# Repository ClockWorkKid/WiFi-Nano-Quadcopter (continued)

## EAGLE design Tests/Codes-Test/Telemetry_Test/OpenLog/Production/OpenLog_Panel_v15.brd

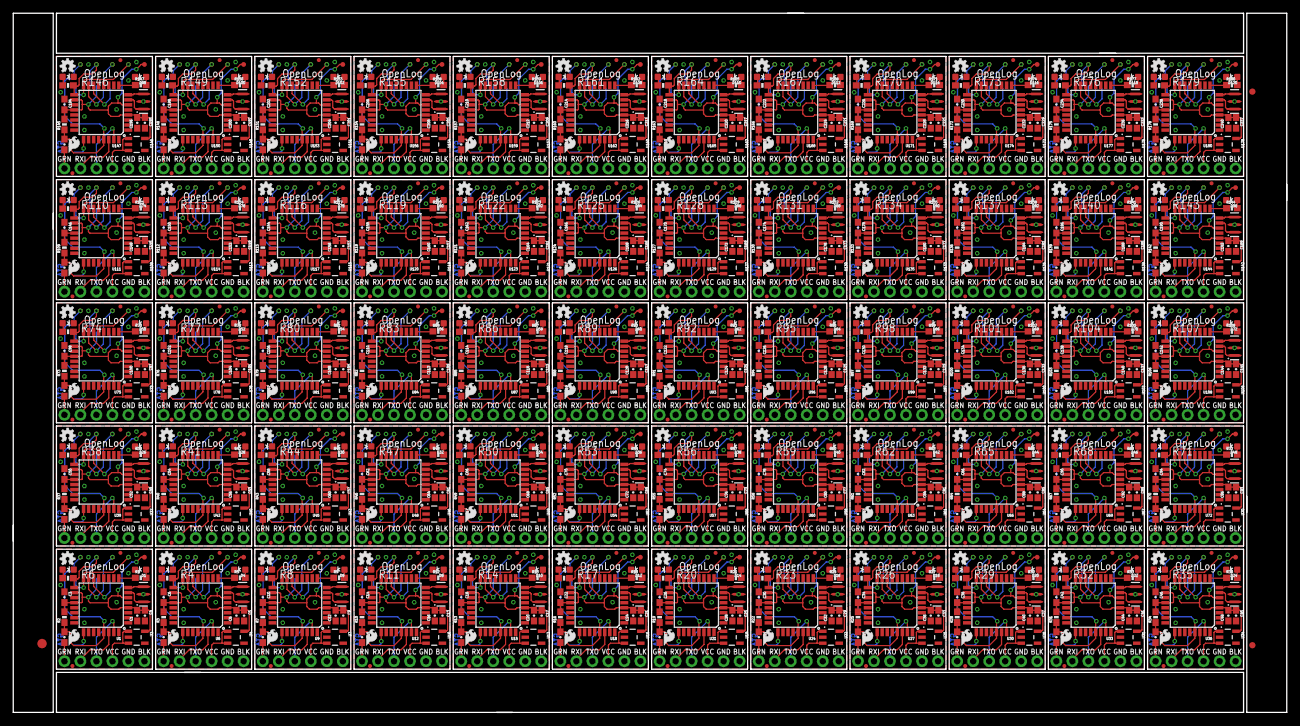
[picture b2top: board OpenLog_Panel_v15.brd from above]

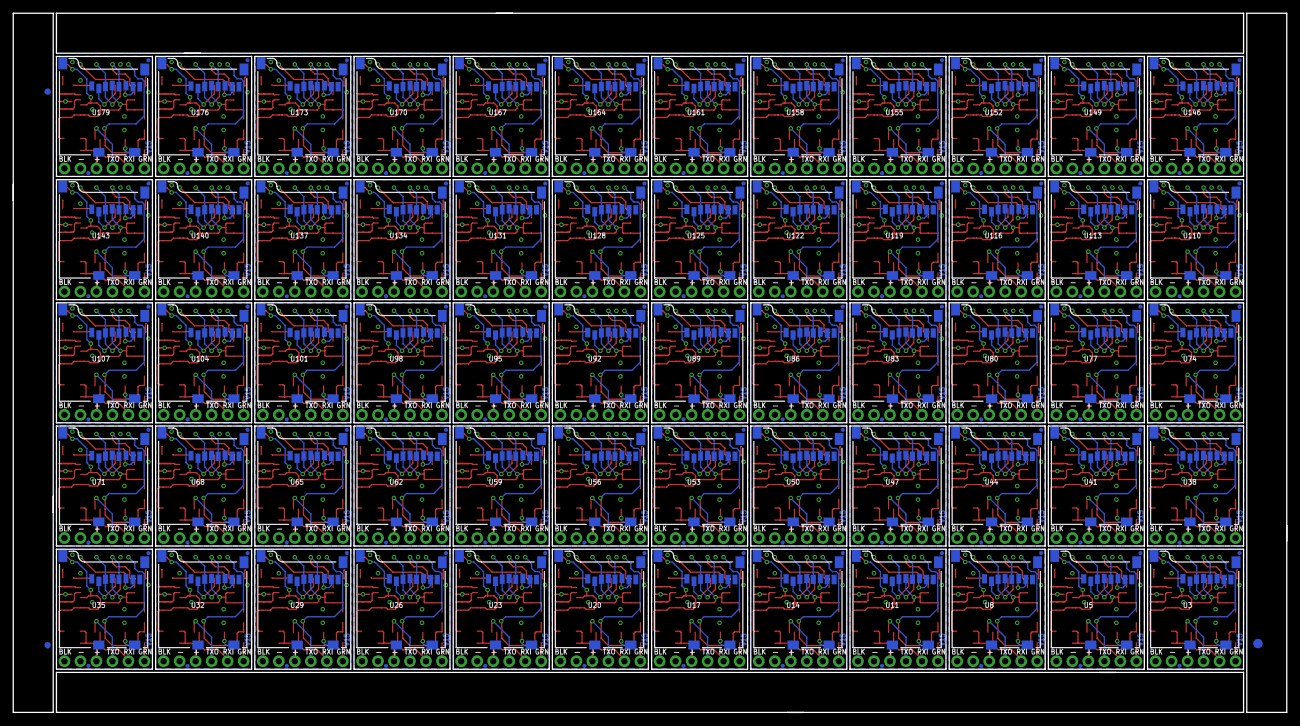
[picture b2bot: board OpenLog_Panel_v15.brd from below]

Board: 2 copper layers, 202.2 x 111.0 mm, 1506 parts (183 on the bottom side), 1020 nets.

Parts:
C1, C8, C12, C16, C20, C24, C28, C32, C36, C40, C44, C48, C52, C56, C60, C64, C68, C72, C76, C80, C84, C88, C92, C96, C100, C104, C108, C112, C116, C120, C124, C128, C132, C136, C140, C144, C148, C152, C156, C160, C164, C168, C172, C176, C180, C184, C188, C192, C196, C200, C204, C208, C212, C216, C220, C224, C228, C232, C236, C240: 10uF; 0603-POL
C2, C3, C4, C5, C6, C7, C9, C10, C11, C13, C14, C15, C17, C18, C19, C21, C22, C23, C25, C26, C27, C29, C30, C31, C33, C34, C35, C37, C38, C39, C41, C42, C43, C45, C46, C47, C49, C50, C51, C53, C54, C55, C57, C58, C59, C61, C62, C63, C65, C66, C67, C69, C70, C71, C73, C74, C75, C77, C78, C79, C81, C82, C83, C85, C86, C87, C89, C90, C91, C93, C94, C95, C97, C98, C99, C101, C102, C103, C105, C106, C107, C109, C110, C111, C113, C114, C115, C117, C118, C119, C121, C122, C123, C125, C126, C127, C129, C130, C131, C133, C134, C135, C137, C138, C139, C141, C142, C143, C145, C146, C147, C149, C150, C151, C153, C154, C155, C157, C158, C159, C161, C162, C163, C165, C166, C167, C169, C170, C171, C173, C174, C175, C177, C178, C179, C181, C182, C183, C185, C186, C187, C189, C190, C191, C193, C194, C195, C197, C198, C199, C201, C202, C203, C205, C206, C207, C209, C210, C211, C213, C214, C215, C217, C218, C219, C221, C222, C223, C225, C226, C227, C229, C230, C231, C233, C234, C235, C237, C238, C239: 0.1uF; 0603-CAP
D1, D4, D6, D8, D10, D12, D14, D16, D18, D20, D22, D24, D26, D28, D30, D32, D34, D36, D38, D40, D42, D44, D46, D48, D50, D52, D54, D56, D58, D60, D62, D64, D66, D68, D70, D72, D74, D76, D78, D80, D82, D84, D86, D88, D90, D92, D94, D96, D98, D100, D102, D104, D106, D108, D110, D112, D114, D116, D118, D120: BLUE; LED-0603
D2, D3, D5, D7, D9, D11, D13, D15, D17, D19, D21, D23, D25, D27, D29, D31, D33, D35, D37, D39, D41, D43, D45, D47, D49, D51, D53, D55, D57, D59, D61, D63, D65, D67, D69, D71, D73, D75, D77, D79, D81, D83, D85, D87, D89, D91, D93, D95, D97, D99, D101, D103, D105, D107, D109, D111, D113, D115, D117, D119: GREEN; LED-0603
E$1, E$2: FIDUCIAL-1.5X3
E$3, E$4, E$7, E$8: FIDUCIAL-1X2
FID1, FID2, FID3, FID4, FID5, FID6, FID7, FID8, FID9, FID10, FID11, FID12, FID13, FID14, FID15, FID16, FID17, FID18, FID19, FID20, FID21, FID22, FID23, FID24, FID25, FID26, FID27, FID28, FID29, FID30, FID31, FID32, FID33, FID34, FID35, FID36, FID37, FID38, FID39, FID40, FID41, FID42, FID43, FID44, FID45, FID46, FID47, FID48, FID49, FID50, FID51, FID52, FID53, FID54, FID55, FID56, FID57, FID58, FID59, FID60, FID61, FID62, FID63, FID64, FID65, FID66, FID67, FID68, FID69, FID70, FID71, FID72, FID73, FID74, FID75, FID76, FID77, FID78, FID79, FID80, FID81, FID82, FID83, FID84, FID85, FID86, FID87, FID88, FID89, FID90, FID91, FID92, FID93, FID94, FID95, FID96, FID97, FID98, FID99, FID100, FID101, FID102, FID103, FID104, FID105, FID106, FID107, FID108, FID109, FID110, FID111, FID112, FID113, FID114, FID115, FID116, FID117, FID118, FID119, FID120, FID121, FID122, FID123, FID124, FID125, FID126, FID127, FID128, FID129, FID130, FID131, FID132, FID133, FID134, FID135, FID136, FID137, FID138, FID139, FID140, FID141, FID142, FID143, FID144, FID145, FID146, FID147, FID148, FID149, FID150, FID151, FID152, FID153, FID154, FID155, FID156, FID157, FID158, FID159, FID160, FID161, FID162, FID163, FID164, FID165, FID166, FID167, FID168, FID169, FID170, FID171, FID172, FID173, FID174, FID175, FID176, FID177, FID178, FID179, FID180, FID181, FID182, FID183, FID184, FID185, FID186, FID187, FID188, FID189, FID190, FID191, FID192, FID193, FID194, FID195, FID196, FID197, FID198, FID199, FID200, FID201, FID202, FID203, FID204, FID205, FID206, FID207, FID208, FID209, FID210, FID211, FID212, FID213, FID214, FID215, FID216, FID217, FID218, FID219, FID220, FID221, FID222, FID223, FID224, FID225, FID226, FID227, FID228, FID229, FID230, FID231, FID232, FID233, FID234, FID235, FID236, FID237, FID238, FID239, FID240: FIDUCIALUFIDUCIAL; MICRO-FIDUCIAL
JP1, JP2, JP3, JP4, JP5, JP6, JP7, JP8, JP9, JP10, JP11, JP12, JP13, JP14, JP15, JP16, JP17, JP18, JP19, JP20, JP21, JP22, JP23, JP24, JP25, JP26, JP27, JP28, JP29, JP30, JP31, JP32, JP33, JP34, JP35, JP36, JP37, JP38, JP39, JP40, JP41, JP42, JP43, JP44, JP45, JP46, JP47, JP48, JP49, JP50, JP51, JP52, JP53, JP54, JP55, JP56, JP57, JP58, JP59, JP60: 1X06_NO_SILK
LOGO1, LOGO3, LOGO5, LOGO7, LOGO9, LOGO11, LOGO13, LOGO15, LOGO17, LOGO19, LOGO21, LOGO23, LOGO25, LOGO27, LOGO29, LOGO31, LOGO33, LOGO35, LOGO37, LOGO39, LOGO41, LOGO43, LOGO45, LOGO47, LOGO49, LOGO51, LOGO53, LOGO55, LOGO57, LOGO59, LOGO61, LOGO63, LOGO65, LOGO67, LOGO69, LOGO71, LOGO73, LOGO75, LOGO77, LOGO79, LOGO81, LOGO83, LOGO85, LOGO87, LOGO89, LOGO91, LOGO93, LOGO95, LOGO97, LOGO99, LOGO101, LOGO103, LOGO105, LOGO107, LOGO109, LOGO111, LOGO113, LOGO115, LOGO117, LOGO119: SFE_LOGO_FLAME.1_INCH; SFE_LOGO_FLAME_.1
LOGO2, LOGO4, LOGO6, LOGO8, LOGO10, LOGO12, LOGO14, LOGO16, LOGO18, LOGO20, LOGO22, LOGO24, LOGO26, LOGO28, LOGO30, LOGO32, LOGO34, LOGO36, LOGO38, LOGO40, LOGO42, LOGO44, LOGO46, LOGO48, LOGO50, LOGO52, LOGO54, LOGO56, LOGO58, LOGO60, LOGO62, LOGO64, LOGO66, LOGO68, LOGO70, LOGO72, LOGO74, LOGO76, LOGO78, LOGO80, LOGO82, LOGO84, LOGO86, LOGO88, LOGO90, LOGO92, LOGO94, LOGO96, LOGO98, LOGO100, LOGO102, LOGO104, LOGO106, LOGO108, LOGO110, LOGO112, LOGO114, LOGO116, LOGO118, LOGO120: OSHW-LOGOMINI; OSHW-LOGO-MINI
Q1, Q2, Q3, Q4, Q5, Q6, Q7, Q8, Q9, Q10, Q11, Q12, Q13, Q14, Q15, Q16, Q17, Q18, Q19, Q20, Q21, Q22, Q23, Q24, Q25, Q26, Q27, Q28, Q29, Q30, Q31, Q32, Q33, Q34, Q35, Q36, Q37, Q38, Q39, Q40, Q41, Q42, Q43, Q44, Q45, Q46, Q47, Q48, Q49, Q50, Q51, Q52, Q53, Q54, Q55, Q56, Q57, Q58, Q59, Q60: 16MHZ; RESONATOR-SMD
R1, R4, R5, R6, R8, R9, R11, R12, R14, R15, R17, R18, R20, R21, R23, R24, R26, R27, R29, R30, R32, R33, R35, R36, R38, R39, R41, R42, R44, R45, R47, R48, R50, R51, R53, R54, R56, R57, R59, R60, R62, R63, R65, R66, R68, R69, R71, R72, R74, R75, R77, R78, R80, R81, R83, R84, R86, R87, R89, R90, R92, R93, R95, R96, R98, R99, R101, R102, R104, R105, R107, R108, R110, R111, R113, R114, R116, R117, R119, R120, R122, R123, R125, R126, R128, R129, R131, R132, R134, R135, R137, R138, R140, R141, R143, R144, R146, R147, R149, R150, R152, R153, R155, R156, R158, R159, R161, R162, R164, R165, R167, R168, R170, R171, R173, R174, R176, R177, R179, R180: 1K; 0603-RES
R2, R3, R7, R10, R13, R16, R19, R22, R25, R28, R31, R34, R37, R40, R43, R46, R49, R52, R55, R58, R61, R64, R67, R70, R73, R76, R79, R82, R85, R88, R91, R94, R97, R100, R103, R106, R109, R112, R115, R118, R121, R124, R127, R130, R133, R136, R139, R142, R145, R148, R151, R154, R157, R160, R163, R166, R169, R172, R175, R178: 10K; 0603-RES
TP1, TP2, TP3, TP4, TP5, TP6, TP7, TP8, TP9, TP10, TP11, TP12, TP13, TP14, TP15, TP16, TP17, TP18, TP19, TP20, TP21, TP22, TP23, TP24, TP25, TP26, TP27, TP28, TP29, TP30, TP31, TP32, TP33, TP34, TP35, TP36, TP37, TP38, TP39, TP40, TP41, TP42, TP43, TP44, TP45, TP46, TP47, TP48, TP49, TP50, TP51, TP52, TP53, TP54, TP55, TP56, TP57, TP58, TP59, TP60, TP61, TP62, TP63, TP64, TP65, TP66, TP67, TP68, TP69, TP70, TP71, TP72, TP73, TP74, TP75, TP76, TP77, TP78, TP79, TP80, TP81, TP82, TP83, TP84, TP85, TP86, TP87, TP88, TP89, TP90, TP91, TP92, TP93, TP94, TP95, TP96, TP97, TP98, TP99, TP100, TP101, TP102, TP103, TP104, TP105, TP106, TP107, TP108, TP109, TP110, TP111, TP112, TP113, TP114, TP115, TP116, TP117, TP118, TP119, TP120, TP121, TP122, TP123, TP124, TP125, TP126, TP127, TP128, TP129, TP130, TP131, TP132, TP133, TP134, TP135, TP136, TP137, TP138, TP139, TP140, TP141, TP142, TP143, TP144, TP145, TP146, TP147, TP148, TP149, TP150, TP151, TP152, TP153, TP154, TP155, TP156, TP157, TP158, TP159, TP160, TP161, TP162, TP163, TP164, TP165, TP166, TP167, TP168, TP169, TP170, TP171, TP172, TP173, TP174, TP175, TP176, TP177, TP178, TP179, TP180, TP181, TP182, TP183, TP184, TP185, TP186, TP187, TP188, TP189, TP190, TP191, TP192, TP193, TP194, TP195, TP196, TP197, TP198, TP199, TP200, TP201, TP202, TP203, TP204, TP205, TP206, TP207, TP208, TP209, TP210, TP211, TP212, TP213, TP214, TP215, TP216, TP217, TP218, TP219, TP220, TP221, TP222, TP223, TP224, TP225, TP226, TP227, TP228, TP229, TP230, TP231, TP232, TP233, TP234, TP235, TP236, TP237, TP238, TP239, TP240, TP241, TP242, TP243, TP244, TP245, TP246, TP247, TP248, TP249, TP250, TP251, TP252, TP253, TP254, TP255, TP256, TP257, TP258, TP259, TP260, TP261, TP262, TP263, TP264, TP265, TP266, TP267, TP268, TP269, TP270, TP271, TP272, TP273, TP274, TP275, TP276, TP277, TP278, TP279, TP280, TP281, TP282, TP283, TP284, TP285, TP286, TP287, TP288, TP289, TP290, TP291, TP292, TP293, TP294, TP295, TP296, TP297, TP298, TP299, TP300: TEST-POINT3; PAD.03X.03
U1, U6, U9, U12, U15, U18, U21, U24, U27, U30, U33, U36, U39, U42, U45, U48, U51, U54, U57, U60, U63, U66, U69, U72, U75, U78, U81, U84, U87, U90, U93, U96, U99, U102, U105, U108, U111, U114, U117, U120, U123, U126, U129, U132, U135, U138, U141, U144, U147, U150, U153, U156, U159, U162, U165, U168, U171, U174, U177, U180: ATMEGA328P_TQFP; TQFP32-08
U2, U4, U7, U10, U13, U16, U19, U22, U25, U28, U31, U34, U37, U40, U43, U46, U49, U52, U55, U58, U61, U64, U67, U70, U73, U76, U79, U82, U85, U88, U91, U94, U97, U100, U103, U106, U109, U112, U115, U118, U121, U124, U127, U130, U133, U136, U139, U142, U145, U148, U151, U154, U157, U160, U163, U166, U169, U172, U175, U178: 3.3V MIC5205; SOT23-5
U3, U5, U8, U11, U14, U17, U20, U23, U26, U29, U32, U35, U38, U41, U44, U47, U50, U53, U56, U59, U62, U65, U68, U71, U74, U77, U80, U83, U86, U89, U92, U95, U98, U101, U104, U107, U110, U113, U116, U119, U122, U125, U128, U131, U134, U137, U140, U143, U146, U149, U152, U155, U158, U161, U164, U167, U170, U173, U176, U179: microSD Socket; MICROSD_1:1

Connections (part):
3.3V: C1.A, C3.2, C4.1, R2.2, TP1.P$1, U1.4, U1.6, U1.18, U1.20, U2.5, U3.4
3.3V1: C5.1, C6.2, C8.A, R3.2, TP6.P$1, U4.5, U5.4, U6.4, U6.6, U6.18, U6.20
3.3V2: C9.1, C10.2, C12.A, R7.2, TP11.P$1, U7.5, U8.4, U9.4, U9.6, U9.18, U9.20
3.3V3: C13.1, C14.2, C16.A, R10.2, TP16.P$1, U10.5, U11.4, U12.4, U12.6, U12.18, U12.20
3.3V4: C17.1, C18.2, C20.A, R13.2, TP21.P$1, U13.5, U14.4, U15.4, U15.6, U15.18, U15.20
3.3V5: C21.1, C22.2, C24.A, R16.2, TP26.P$1, U16.5, U17.4, U18.4, U18.6, U18.18, U18.20
3.3V6: C25.1, C26.2, C28.A, R19.2, TP31.P$1, U19.5, U20.4, U21.4, U21.6, U21.18, U21.20
3.3V7: C29.1, C30.2, C32.A, R22.2, TP36.P$1, U22.5, U23.4, U24.4, U24.6, U24.18, U24.20
3.3V8: C33.1, C34.2, C36.A, R25.2, TP41.P$1, U25.5, U26.4, U27.4, U27.6, U27.18, U27.20
3.3V9: C37.1, C38.2, C40.A, R28.2, TP46.P$1, U28.5, U29.4, U30.4, U30.6, U30.18, U30.20
3.3V10: C41.1, C42.2, C44.A, R31.2, TP51.P$1, U31.5, U32.4, U33.4, U33.6, U33.18, U33.20
3.3V11: C45.1, C46.2, C48.A, R34.2, TP56.P$1, U34.5, U35.4, U36.4, U36.6, U36.18, U36.20
3.3V12: C49.1, C50.2, C52.A, R37.2, TP61.P$1, U37.5, U38.4, U39.4, U39.6, U39.18, U39.20
3.3V13: C53.1, C54.2, C56.A, R40.2, TP66.P$1, U40.5, U41.4, U42.4, U42.6, U42.18, U42.20
3.3V14: C57.1, C58.2, C60.A, R43.2, TP71.P$1, U43.5, U44.4, U45.4, U45.6, U45.18, U45.20
3.3V15: C61.1, C62.2, C64.A, R46.2, TP76.P$1, U46.5, U47.4, U48.4, U48.6, U48.18, U48.20
3.3V16: C65.1, C66.2, C68.A, R49.2, TP81.P$1, U49.5, U50.4, U51.4, U51.6, U51.18, U51.20
3.3V17: C69.1, C70.2, C72.A, R52.2, TP86.P$1, U52.5, U53.4, U54.4, U54.6, U54.18, U54.20
3.3V18: C73.1, C74.2, C76.A, R55.2, TP91.P$1, U55.5, U56.4, U57.4, U57.6, U57.18, U57.20
3.3V19: C77.1, C78.2, C80.A, R58.2, TP96.P$1, U58.5, U59.4, U60.4, U60.6, U60.18, U60.20
3.3V20: C81.1, C82.2, C84.A, R61.2, TP101.P$1, U61.5, U62.4, U63.4, U63.6, U63.18, U63.20
3.3V21: C85.1, C86.2, C88.A, R64.2, TP106.P$1, U64.5, U65.4, U66.4, U66.6, U66.18, U66.20
3.3V22: C89.1, C90.2, C92.A, R67.2, TP111.P$1, U67.5, U68.4, U69.4, U69.6, U69.18, U69.20
3.3V23: C93.1, C94.2, C96.A, R70.2, TP116.P$1, U70.5, U71.4, U72.4, U72.6, U72.18, U72.20
3.3V24: C97.1, C98.2, C100.A, R73.2, TP121.P$1, U73.5, U74.4, U75.4, U75.6, U75.18, U75.20
3.3V25: C101.1, C102.2, C104.A, R76.2, TP126.P$1, U76.5, U77.4, U78.4, U78.6, U78.18, U78.20
3.3V26: C105.1, C106.2, C108.A, R79.2, TP131.P$1, U79.5, U80.4, U81.4, U81.6, U81.18, U81.20
3.3V27: C109.1, C110.2, C112.A, R82.2, TP136.P$1, U82.5, U83.4, U84.4, U84.6, U84.18, U84.20
3.3V28: C113.1, C114.2, C116.A, R85.2, TP141.P$1, U85.5, U86.4, U87.4, U87.6, U87.18, U87.20
3.3V29: C117.1, C118.2, C120.A, R88.2, TP146.P$1, U88.5, U89.4, U90.4, U90.6, U90.18, U90.20
3.3V30: C121.1, C122.2, C124.A, R91.2, TP151.P$1, U91.5, U92.4, U93.4, U93.6, U93.18, U93.20
3.3V31: C125.1, C126.2, C128.A, R94.2, TP156.P$1, U94.5, U95.4, U96.4, U96.6, U96.18, U96.20
3.3V32: C129.1, C130.2, C132.A, R97.2, TP161.P$1, U97.5, U98.4, U99.4, U99.6, U99.18, U99.20
3.3V33: C133.1, C134.2, C136.A, R100.2, TP166.P$1, U100.5, U101.4, U102.4, U102.6, U102.18, U102.20
3.3V34: C137.1, C138.2, C140.A, R103.2, TP171.P$1, U103.5, U104.4, U105.4, U105.6, U105.18, U105.20
3.3V35: C141.1, C142.2, C144.A, R106.2, TP176.P$1, U106.5, U107.4, U108.4, U108.6, U108.18, U108.20
3.3V36: C145.1, C146.2, C148.A, R109.2, TP181.P$1, U109.5, U110.4, U111.4, U111.6, U111.18, U111.20
3.3V37: C149.1, C150.2, C152.A, R112.2, TP186.P$1, U112.5, U113.4, U114.4, U114.6, U114.18, U114.20
3.3V38: C153.1, C154.2, C156.A, R115.2, TP191.P$1, U115.5, U116.4, U117.4, U117.6, U117.18, U117.20
3.3V39: C157.1, C158.2, C160.A, R118.2, TP196.P$1, U118.5, U119.4, U120.4, U120.6, U120.18, U120.20
3.3V40: C161.1, C162.2, C164.A, R121.2, TP201.P$1, U121.5, U122.4, U123.4, U123.6, U123.18, U123.20
3.3V41: C165.1, C166.2, C168.A, R124.2, TP206.P$1, U124.5, U125.4, U126.4, U126.6, U126.18, U126.20
3.3V42: C169.1, C170.2, C172.A, R127.2, TP211.P$1, U127.5, U128.4, U129.4, U129.6, U129.18, U129.20
3.3V43: C173.1, C174.2, C176.A, R130.2, TP216.P$1, U130.5, U131.4, U132.4, U132.6, U132.18, U132.20
3.3V44: C177.1, C178.2, C180.A, R133.2, TP221.P$1, U133.5, U134.4, U135.4, U135.6, U135.18, U135.20
3.3V45: C181.1, C182.2, C184.A, R136.2, TP226.P$1, U136.5, U137.4, U138.4, U138.6, U138.18, U138.20
3.3V46: C185.1, C186.2, C188.A, R139.2, TP231.P$1, U139.5, U140.4, U141.4, U141.6, U141.18, U141.20
3.3V47: C189.1, C190.2, C192.A, R142.2, TP236.P$1, U142.5, U143.4, U144.4, U144.6, U144.18, U144.20
3.3V48: C193.1, C194.2, C196.A, R145.2, TP241.P$1, U145.5, U146.4, U147.4, U147.6, U147.18, U147.20
3.3V49: C197.1, C198.2, C200.A, R148.2, TP246.P$1, U148.5, U149.4, U150.4, U150.6, U150.18, U150.20
3.3V50: C201.1, C202.2, C204.A, R151.2, TP251.P$1, U151.5, U152.4, U153.4, U153.6, U153.18, U153.20
3.3V51: C205.1, C206.2, C208.A, R154.2, TP256.P$1, U154.5, U155.4, U156.4, U156.6, U156.18, U156.20
3.3V52: C209.1, C210.2, C212.A, R157.2, TP261.P$1, U157.5, U158.4, U159.4, U159.6, U159.18, U159.20
3.3V53: C213.1, C214.2, C216.A, R160.2, TP266.P$1, U160.5, U161.4, U162.4, U162.6, U162.18, U162.20
3.3V54: C217.1, C218.2, C220.A, R163.2, TP271.P$1, U163.5, U164.4, U165.4, U165.6, U165.18, U165.20
3.3V55: C221.1, C222.2, C224.A, R166.2, TP276.P$1, U166.5, U167.4, U168.4, U168.6, U168.18, U168.20
3.3V56: C225.1, C226.2, C228.A, R169.2, TP281.P$1, U169.5, U170.4, U171.4, U171.6, U171.18, U171.20
3.3V57: C229.1, C230.2, C232.A, R172.2, TP286.P$1, U172.5, U173.4, U174.4, U174.6, U174.18, U174.20
3.3V58: C233.1, C234.2, C236.A, R175.2, TP291.P$1, U175.5, U176.4, U177.4, U177.6, U177.18, U177.20
3.3V59: C237.1, C238.2, C240.A, R178.2, TP296.P$1, U178.5, U179.4, U180.4, U180.6, U180.18, U180.20
CD: U1.25, U3.CD1
CD1: U5.CD1, U6.25
CD2: U8.CD1, U9.25
CD3: U11.CD1, U12.25
CD4: U14.CD1, U15.25
CD5: U17.CD1, U18.25
CD6: U20.CD1, U21.25
CD7: U23.CD1, U24.25
CD8: U26.CD1, U27.25
CD9: U29.CD1, U30.25
CD10: U32.CD1, U33.25
CD11: U35.CD1, U36.25
CD12: U38.CD1, U39.25
CD13: U41.CD1, U42.25
CD14: U44.CD1, U45.25
CD15: U47.CD1, U48.25
CD16: U50.CD1, U51.25
CD17: U53.CD1, U54.25
CD18: U56.CD1, U57.25
CD19: U59.CD1, U60.25
CD20: U62.CD1, U63.25
CD21: U65.CD1, U66.25
CD22: U68.CD1, U69.25
CD23: U71.CD1, U72.25
CD24: U74.CD1, U75.25
CD25: U77.CD1, U78.25
CD26: U80.CD1, U81.25
CD27: U83.CD1, U84.25
CD28: U86.CD1, U87.25
CD29: U89.CD1, U90.25
CD30: U92.CD1, U93.25
CD31: U95.CD1, U96.25
CD32: U98.CD1, U99.25
CD33: U101.CD1, U102.25
CD34: U104.CD1, U105.25
CD35: U107.CD1, U108.25
CD36: U110.CD1, U111.25
CD37: U113.CD1, U114.25
CD38: U116.CD1, U117.25
CD39: U119.CD1, U120.25
CD40: U122.CD1, U123.25
CD41: U125.CD1, U126.25
CD42: U128.CD1, U129.25
CD43: U131.CD1, U132.25
CD44: U134.CD1, U135.25
CD45: U137.CD1, U138.25
CD46: U140.CD1, U141.25
CD47: U143.CD1, U144.25
CD48: U146.CD1, U147.25
CD49: U149.CD1, U150.25
CD50: U152.CD1, U153.25
CD51: U155.CD1, U156.25
CD52: U158.CD1, U159.25
CD53: U161.CD1, U162.25
CD54: U164.CD1, U165.25
CD55: U167.CD1, U168.25
CD56: U170.CD1, U171.25
CD57: U173.CD1, U174.25
CD58: U176.CD1, U177.25
CD59: U179.CD1, U180.25
CS: U1.14, U3.2
CS1: U5.2, U6.14
CS2: U8.2, U9.14
CS3: U11.2, U12.14
CS4: U14.2, U15.14
CS5: U17.2, U18.14
CS6: U20.2, U21.14
CS7: U23.2, U24.14
CS8: U26.2, U27.14
CS9: U29.2, U30.14
CS10: U32.2, U33.14
CS11: U35.2, U36.14
CS12: U38.2, U39.14
CS13: U41.2, U42.14
CS14: U44.2, U45.14
CS15: U47.2, U48.14
CS16: U50.2, U51.14
CS17: U53.2, U54.14
CS18: U56.2, U57.14
CS19: U59.2, U60.14
CS20: U62.2, U63.14
CS21: U65.2, U66.14
CS22: U68.2, U69.14
CS23: U71.2, U72.14
CS24: U74.2, U75.14
CS25: U77.2, U78.14
CS26: U80.2, U81.14
CS27: U83.2, U84.14
CS28: U86.2, U87.14
CS29: U89.2, U90.14
CS30: U92.2, U93.14
CS31: U95.2, U96.14
CS32: U98.2, U99.14
CS33: U101.2, U102.14
CS34: U104.2, U105.14
CS35: U107.2, U108.14
CS36: U110.2, U111.14
CS37: U113.2, U114.14
CS38: U116.2, U117.14
CS39: U119.2, U120.14
CS40: U122.2, U123.14
CS41: U125.2, U126.14
CS42: U128.2, U129.14
CS43: U131.2, U132.14
CS44: U134.2, U135.14
CS45: U137.2, U138.14
CS46: U140.2, U141.14
CS47: U143.2, U144.14
CS48: U146.2, U147.14
CS49: U149.2, U150.14
CS50: U152.2, U153.14
CS51: U155.2, U156.14
CS52: U158.2, U159.14
CS53: U161.2, U162.14
CS54: U164.2, U165.14
CS55: U167.2, U168.14
CS56: U170.2, U171.14
CS57: U173.2, U174.14
CS58: U176.2, U177.14
CS59: U179.2, U180.14
DTR: C2.2, JP2.6
DTR1: C7.2, JP1.6
DTR2: C11.2, JP3.6
DTR3: C15.2, JP4.6
DTR4: C19.2, JP5.6
DTR5: C23.2, JP6.6
DTR6: C27.2, JP7.6
DTR7: C31.2, JP8.6
DTR8: C35.2, JP9.6
DTR9: C39.2, JP10.6
DTR10: C43.2, JP11.6
DTR11: C47.2, JP12.6
DTR12: C51.2, JP13.6
DTR13: C55.2, JP14.6
DTR14: C59.2, JP15.6
DTR15: C63.2, JP16.6
DTR16: C67.2, JP17.6
DTR17: C71.2, JP18.6
DTR18: C75.2, JP19.6
DTR19: C79.2, JP20.6
DTR20: C83.2, JP21.6
DTR21: C87.2, JP22.6
DTR22: C91.2, JP23.6
DTR23: C95.2, JP24.6
DTR24: C99.2, JP25.6
DTR25: C103.2, JP26.6
DTR26: C107.2, JP27.6
DTR27: C111.2, JP28.6
DTR28: C115.2, JP29.6
DTR29: C119.2, JP30.6
DTR30: C123.2, JP31.6
DTR31: C127.2, JP32.6
DTR32: C131.2, JP33.6
DTR33: C135.2, JP34.6
DTR34: C139.2, JP35.6
DTR35: C143.2, JP36.6
DTR36: C147.2, JP37.6
DTR37: C151.2, JP38.6
DTR38: C155.2, JP39.6
DTR39: C159.2, JP40.6
DTR40: C163.2, JP41.6
DTR41: C167.2, JP42.6
DTR42: C171.2, JP43.6
DTR43: C175.2, JP44.6
DTR44: C179.2, JP45.6
DTR45: C183.2, JP46.6
DTR46: C187.2, JP47.6
DTR47: C191.2, JP48.6
DTR48: C195.2, JP49.6
DTR49: C199.2, JP50.6
DTR50: C203.2, JP51.6
DTR51: C207.2, JP52.6
DTR52: C211.2, JP53.6
DTR53: C215.2, JP54.6
DTR54: C219.2, JP55.6
DTR55: C223.2, JP56.6
DTR56: C227.2, JP57.6
DTR57: C231.2, JP58.6
DTR58: C235.2, JP59.6
DTR59: C239.2, JP60.6
GND: C1.K, C3.1, C4.2, D1.C, D3.C, JP2.1, JP2.2, Q1.2, U1.3, U1.5, U1.21, U2.2, U3.6, U3.GND1, U3.GND3
GND1: C5.2, C6.1, C8.K, D2.C, D4.C, JP1.1, JP1.2, Q2.2, U4.2, U5.6, U5.GND1, U5.GND3, U6.3, U6.5, U6.21
GND2: C9.2, C10.1, C12.K, D5.C, D6.C, JP3.1, JP3.2, Q3.2, U7.2, U8.6, U8.GND1, U8.GND3, U9.3, U9.5, U9.21
GND3: C13.2, C14.1, C16.K, D7.C, D8.C, JP4.1, JP4.2, Q4.2, U10.2, U11.6, U11.GND1, U11.GND3, U12.3, U12.5, U12.21
GND4: C17.2, C18.1, C20.K, D9.C, D10.C, JP5.1, JP5.2, Q5.2, U13.2, U14.6, U14.GND1, U14.GND3, U15.3, U15.5, U15.21
GND5: C21.2, C22.1, C24.K, D11.C, D12.C, JP6.1, JP6.2, Q6.2, U16.2, U17.6, U17.GND1, U17.GND3, U18.3, U18.5, U18.21
GND6: C25.2, C26.1, C28.K, D13.C, D14.C, JP7.1, JP7.2, Q7.2, U19.2, U20.6, U20.GND1, U20.GND3, U21.3, U21.5, U21.21
GND7: C29.2, C30.1, C32.K, D15.C, D16.C, JP8.1, JP8.2, Q8.2, U22.2, U23.6, U23.GND1, U23.GND3, U24.3, U24.5, U24.21
GND8: C33.2, C34.1, C36.K, D17.C, D18.C, JP9.1, JP9.2, Q9.2, U25.2, U26.6, U26.GND1, U26.GND3, U27.3, U27.5, U27.21
GND9: C37.2, C38.1, C40.K, D19.C, D20.C, JP10.1, JP10.2, Q10.2, U28.2, U29.6, U29.GND1, U29.GND3, U30.3, U30.5, U30.21
GND10: C41.2, C42.1, C44.K, D21.C, D22.C, JP11.1, JP11.2, Q11.2, U31.2, U32.6, U32.GND1, U32.GND3, U33.3, U33.5, U33.21
GND11: C45.2, C46.1, C48.K, D23.C, D24.C, JP12.1, JP12.2, Q12.2, U34.2, U35.6, U35.GND1, U35.GND3, U36.3, U36.5, U36.21
GND12: C49.2, C50.1, C52.K, D25.C, D26.C, JP13.1, JP13.2, Q13.2, U37.2, U38.6, U38.GND1, U38.GND3, U39.3, U39.5, U39.21
GND13: C53.2, C54.1, C56.K, D27.C, D28.C, JP14.1, JP14.2, Q14.2, U40.2, U41.6, U41.GND1, U41.GND3, U42.3, U42.5, U42.21
GND14: C57.2, C58.1, C60.K, D29.C, D30.C, JP15.1, JP15.2, Q15.2, U43.2, U44.6, U44.GND1, U44.GND3, U45.3, U45.5, U45.21
GND15: C61.2, C62.1, C64.K, D31.C, D32.C, JP16.1, JP16.2, Q16.2, U46.2, U47.6, U47.GND1, U47.GND3, U48.3, U48.5, U48.21
GND16: C65.2, C66.1, C68.K, D33.C, D34.C, JP17.1, JP17.2, Q17.2, U49.2, U50.6, U50.GND1, U50.GND3, U51.3, U51.5, U51.21
GND17: C69.2, C70.1, C72.K, D35.C, D36.C, JP18.1, JP18.2, Q18.2, U52.2, U53.6, U53.GND1, U53.GND3, U54.3, U54.5, U54.21
GND18: C73.2, C74.1, C76.K, D37.C, D38.C, JP19.1, JP19.2, Q19.2, U55.2, U56.6, U56.GND1, U56.GND3, U57.3, U57.5, U57.21
GND19: C77.2, C78.1, C80.K, D39.C, D40.C, JP20.1, JP20.2, Q20.2, U58.2, U59.6, U59.GND1, U59.GND3, U60.3, U60.5, U60.21
GND20: C81.2, C82.1, C84.K, D41.C, D42.C, JP21.1, JP21.2, Q21.2, U61.2, U62.6, U62.GND1, U62.GND3, U63.3, U63.5, U63.21
GND21: C85.2, C86.1, C88.K, D43.C, D44.C, JP22.1, JP22.2, Q22.2, U64.2, U65.6, U65.GND1, U65.GND3, U66.3, U66.5, U66.21
GND22: C89.2, C90.1, C92.K, D45.C, D46.C, JP23.1, JP23.2, Q23.2, U67.2, U68.6, U68.GND1, U68.GND3, U69.3, U69.5, U69.21
GND23: C93.2, C94.1, C96.K, D47.C, D48.C, JP24.1, JP24.2, Q24.2, U70.2, U71.6, U71.GND1, U71.GND3, U72.3, U72.5, U72.21
GND24: C97.2, C98.1, C100.K, D49.C, D50.C, JP25.1, JP25.2, Q25.2, U73.2, U74.6, U74.GND1, U74.GND3, U75.3, U75.5, U75.21
GND25: C101.2, C102.1, C104.K, D51.C, D52.C, JP26.1, JP26.2, Q26.2, U76.2, U77.6, U77.GND1, U77.GND3, U78.3, U78.5, U78.21
GND26: C105.2, C106.1, C108.K, D53.C, D54.C, JP27.1, JP27.2, Q27.2, U79.2, U80.6, U80.GND1, U80.GND3, U81.3, U81.5, U81.21
GND27: C109.2, C110.1, C112.K, D55.C, D56.C, JP28.1, JP28.2, Q28.2, U82.2, U83.6, U83.GND1, U83.GND3, U84.3, U84.5, U84.21
GND28: C113.2, C114.1, C116.K, D57.C, D58.C, JP29.1, JP29.2, Q29.2, U85.2, U86.6, U86.GND1, U86.GND3, U87.3, U87.5, U87.21
GND29: C117.2, C118.1, C120.K, D59.C, D60.C, JP30.1, JP30.2, Q30.2, U88.2, U89.6, U89.GND1, U89.GND3, U90.3, U90.5, U90.21
GND30: C121.2, C122.1, C124.K, D61.C, D62.C, JP31.1, JP31.2, Q31.2, U91.2, U92.6, U92.GND1, U92.GND3, U93.3, U93.5, U93.21
GND31: C125.2, C126.1, C128.K, D63.C, D64.C, JP32.1, JP32.2, Q32.2, U94.2, U95.6, U95.GND1, U95.GND3, U96.3, U96.5, U96.21
GND32: C129.2, C130.1, C132.K, D65.C, D66.C, JP33.1, JP33.2, Q33.2, U97.2, U98.6, U98.GND1, U98.GND3, U99.3, U99.5, U99.21
GND33: C133.2, C134.1, C136.K, D67.C, D68.C, JP34.1, JP34.2, Q34.2, U100.2, U101.6, U101.GND1, U101.GND3, U102.3, U102.5, U102.21
GND34: C137.2, C138.1, C140.K, D69.C, D70.C, JP35.1, JP35.2, Q35.2, U103.2, U104.6, U104.GND1, U104.GND3, U105.3, U105.5, U105.21
GND35: C141.2, C142.1, C144.K, D71.C, D72.C, JP36.1, JP36.2, Q36.2, U106.2, U107.6, U107.GND1, U107.GND3, U108.3, U108.5, U108.21
GND36: C145.2, C146.1, C148.K, D73.C, D74.C, JP37.1, JP37.2, Q37.2, U109.2, U110.6, U110.GND1, U110.GND3, U111.3, U111.5, U111.21
GND37: C149.2, C150.1, C152.K, D75.C, D76.C, JP38.1, JP38.2, Q38.2, U112.2, U113.6, U113.GND1, U113.GND3, U114.3, U114.5, U114.21
GND38: C153.2, C154.1, C156.K, D77.C, D78.C, JP39.1, JP39.2, Q39.2, U115.2, U116.6, U116.GND1, U116.GND3, U117.3, U117.5, U117.21
GND39: C157.2, C158.1, C160.K, D79.C, D80.C, JP40.1, JP40.2, Q40.2, U118.2, U119.6, U119.GND1, U119.GND3, U120.3, U120.5, U120.21
GND40: C161.2, C162.1, C164.K, D81.C, D82.C, JP41.1, JP41.2, Q41.2, U121.2, U122.6, U122.GND1, U122.GND3, U123.3, U123.5, U123.21
GND41: C165.2, C166.1, C168.K, D83.C, D84.C, JP42.1, JP42.2, Q42.2, U124.2, U125.6, U125.GND1, U125.GND3, U126.3, U126.5, U126.21
GND42: C169.2, C170.1, C172.K, D85.C, D86.C, JP43.1, JP43.2, Q43.2, U127.2, U128.6, U128.GND1, U128.GND3, U129.3, U129.5, U129.21
GND43: C173.2, C174.1, C176.K, D87.C, D88.C, JP44.1, JP44.2, Q44.2, U130.2, U131.6, U131.GND1, U131.GND3, U132.3, U132.5, U132.21
GND44: C177.2, C178.1, C180.K, D89.C, D90.C, JP45.1, JP45.2, Q45.2, U133.2, U134.6, U134.GND1, U134.GND3, U135.3, U135.5, U135.21
GND45: C181.2, C182.1, C184.K, D91.C, D92.C, JP46.1, JP46.2, Q46.2, U136.2, U137.6, U137.GND1, U137.GND3, U138.3, U138.5, U138.21
GND46: C185.2, C186.1, C188.K, D93.C, D94.C, JP47.1, JP47.2, Q47.2, U139.2, U140.6, U140.GND1, U140.GND3, U141.3, U141.5, U141.21
GND47: C189.2, C190.1, C192.K, D95.C, D96.C, JP48.1, JP48.2, Q48.2, U142.2, U143.6, U143.GND1, U143.GND3, U144.3, U144.5, U144.21
GND48: C193.2, C194.1, C196.K, D97.C, D98.C, JP49.1, JP49.2, Q49.2, U145.2, U146.6, U146.GND1, U146.GND3, U147.3, U147.5, U147.21
GND49: C197.2, C198.1, C200.K, D99.C, D100.C, JP50.1, JP50.2, Q50.2, U148.2, U149.6, U149.GND1, U149.GND3, U150.3, U150.5, U150.21
GND50: C201.2, C202.1, C204.K, D101.C, D102.C, JP51.1, JP51.2, Q51.2, U151.2, U152.6, U152.GND1, U152.GND3, U153.3, U153.5, U153.21
GND51: C205.2, C206.1, C208.K, D103.C, D104.C, JP52.1, JP52.2, Q52.2, U154.2, U155.6, U155.GND1, U155.GND3, U156.3, U156.5, U156.21
GND52: C209.2, C210.1, C212.K, D105.C, D106.C, JP53.1, JP53.2, Q53.2, U157.2, U158.6, U158.GND1, U158.GND3, U159.3, U159.5, U159.21
GND53: C213.2, C214.1, C216.K, D107.C, D108.C, JP54.1, JP54.2, Q54.2, U160.2, U161.6, U161.GND1, U161.GND3, U162.3, U162.5, U162.21
GND54: C217.2, C218.1, C220.K, D109.C, D110.C, JP55.1, JP55.2, Q55.2, U163.2, U164.6, U164.GND1, U164.GND3, U165.3, U165.5, U165.21
GND55: C221.2, C222.1, C224.K, D111.C, D112.C, JP56.1, JP56.2, Q56.2, U166.2, U167.6, U167.GND1, U167.GND3, U168.3, U168.5, U168.21
GND56: C225.2, C226.1, C228.K, D113.C, D114.C, JP57.1, JP57.2, Q57.2, U169.2, U170.6, U170.GND1, U170.GND3, U171.3, U171.5, U171.21
GND57: C229.2, C230.1, C232.K, D115.C, D116.C, JP58.1, JP58.2, Q58.2, U172.2, U173.6, U173.GND1, U173.GND3, U174.3, U174.5, U174.21
GND58: C233.2, C234.1, C236.K, D117.C, D118.C, JP59.1, JP59.2, Q59.2, U175.2, U176.6, U176.GND1, U176.GND3, U177.3, U177.5, U177.21
GND59: C237.2, C238.1, C240.K, D119.C, D120.C, JP60.1, JP60.2, Q60.2, U178.2, U179.6, U179.GND1, U179.GND3, U180.3, U180.5, U180.21
MISO: TP2.P$1, U1.16, U3.7
MISO1: TP7.P$1, U5.7, U6.16
MISO2: TP12.P$1, U8.7, U9.16
MISO3: TP17.P$1, U11.7, U12.16
MISO4: TP22.P$1, U14.7, U15.16
MISO5: TP27.P$1, U17.7, U18.16
MISO6: TP32.P$1, U20.7, U21.16
MISO7: TP37.P$1, U23.7, U24.16
MISO8: TP42.P$1, U26.7, U27.16
MISO9: TP47.P$1, U29.7, U30.16
MISO10: TP52.P$1, U32.7, U33.16
MISO11: TP57.P$1, U35.7, U36.16
MISO12: TP62.P$1, U38.7, U39.16
MISO13: TP67.P$1, U41.7, U42.16
MISO14: TP72.P$1, U44.7, U45.16
MISO15: TP77.P$1, U47.7, U48.16
MISO16: TP82.P$1, U50.7, U51.16
MISO17: TP87.P$1, U53.7, U54.16
MISO18: TP92.P$1, U56.7, U57.16
MISO19: TP97.P$1, U59.7, U60.16
MISO20: TP102.P$1, U62.7, U63.16
MISO21: TP107.P$1, U65.7, U66.16
MISO22: TP112.P$1, U68.7, U69.16
MISO23: TP117.P$1, U71.7, U72.16
MISO24: TP122.P$1, U74.7, U75.16
MISO25: TP127.P$1, U77.7, U78.16
MISO26: TP132.P$1, U80.7, U81.16
MISO27: TP137.P$1, U83.7, U84.16
MISO28: TP142.P$1, U86.7, U87.16
MISO29: TP147.P$1, U89.7, U90.16
MISO30: TP152.P$1, U92.7, U93.16
MISO31: TP157.P$1, U95.7, U96.16
MISO32: TP162.P$1, U98.7, U99.16
MISO33: TP167.P$1, U101.7, U102.16
MISO34: TP172.P$1, U104.7, U105.16
MISO35: TP177.P$1, U107.7, U108.16
MISO36: TP182.P$1, U110.7, U111.16
MISO37: TP187.P$1, U113.7, U114.16
MISO38: TP192.P$1, U116.7, U117.16
MISO39: TP197.P$1, U119.7, U120.16
MISO40: TP202.P$1, U122.7, U123.16
MISO41: TP207.P$1, U125.7, U126.16
MISO42: TP212.P$1, U128.7, U129.16
MISO43: TP217.P$1, U131.7, U132.16
MISO44: TP222.P$1, U134.7, U135.16
MISO45: TP227.P$1, U137.7, U138.16
MISO46: TP232.P$1, U140.7, U141.16
MISO47: TP237.P$1, U143.7, U144.16
MISO48: TP242.P$1, U146.7, U147.16
MISO49: TP247.P$1, U149.7, U150.16
MISO50: TP252.P$1, U152.7, U153.16
MISO51: TP257.P$1, U155.7, U156.16
MISO52: TP262.P$1, U158.7, U159.16
MISO53: TP267.P$1, U161.7, U162.16
MISO54: TP272.P$1, U164.7, U165.16
MISO55: TP277.P$1, U167.7, U168.16
MISO56: TP282.P$1, U170.7, U171.16
MISO57: TP287.P$1, U173.7, U174.16
MISO58: TP292.P$1, U176.7, U177.16
MISO59: TP297.P$1, U179.7, U180.16
MOSI: TP3.P$1, U1.15, U3.3
MOSI1: TP8.P$1, U5.3, U6.15
MOSI2: TP13.P$1, U8.3, U9.15
MOSI3: TP18.P$1, U11.3, U12.15
MOSI4: TP23.P$1, U14.3, U15.15
MOSI5: TP28.P$1, U17.3, U18.15
MOSI6: TP33.P$1, U20.3, U21.15
MOSI7: TP38.P$1, U23.3, U24.15
MOSI8: TP43.P$1, U26.3, U27.15
MOSI9: TP48.P$1, U29.3, U30.15
MOSI10: TP53.P$1, U32.3, U33.15
MOSI11: TP58.P$1, U35.3, U36.15
MOSI12: TP63.P$1, U38.3, U39.15
MOSI13: TP68.P$1, U41.3, U42.15
MOSI14: TP73.P$1, U44.3, U45.15
MOSI15: TP78.P$1, U47.3, U48.15
MOSI16: TP83.P$1, U50.3, U51.15
MOSI17: TP88.P$1, U53.3, U54.15
MOSI18: TP93.P$1, U56.3, U57.15
MOSI19: TP98.P$1, U59.3, U60.15
MOSI20: TP103.P$1, U62.3, U63.15
MOSI21: TP108.P$1, U65.3, U66.15
MOSI22: TP113.P$1, U68.3, U69.15
MOSI23: TP118.P$1, U71.3, U72.15
MOSI24: TP123.P$1, U74.3, U75.15
MOSI25: TP128.P$1, U77.3, U78.15
MOSI26: TP133.P$1, U80.3, U81.15
MOSI27: TP138.P$1, U83.3, U84.15
MOSI28: TP143.P$1, U86.3, U87.15
MOSI29: TP148.P$1, U89.3, U90.15
MOSI30: TP153.P$1, U92.3, U93.15
MOSI31: TP158.P$1, U95.3, U96.15
MOSI32: TP163.P$1, U98.3, U99.15
MOSI33: TP168.P$1, U101.3, U102.15
MOSI34: TP173.P$1, U104.3, U105.15
MOSI35: TP178.P$1, U107.3, U108.15
MOSI36: TP183.P$1, U110.3, U111.15
MOSI37: TP188.P$1, U113.3, U114.15
MOSI38: TP193.P$1, U116.3, U117.15
MOSI39: TP198.P$1, U119.3, U120.15
MOSI40: TP203.P$1, U122.3, U123.15
MOSI41: TP208.P$1, U125.3, U126.15
MOSI42: TP213.P$1, U128.3, U129.15
MOSI43: TP218.P$1, U131.3, U132.15
MOSI44: TP223.P$1, U134.3, U135.15
MOSI45: TP228.P$1, U137.3, U138.15
MOSI46: TP233.P$1, U140.3, U141.15
MOSI47: TP238.P$1, U143.3, U144.15
MOSI48: TP243.P$1, U146.3, U147.15
MOSI49: TP248.P$1, U149.3, U150.15
MOSI50: TP253.P$1, U152.3, U153.15
MOSI51: TP258.P$1, U155.3, U156.15
MOSI52: TP263.P$1, U158.3, U159.15
MOSI53: TP268.P$1, U161.3, U162.15
MOSI54: TP273.P$1, U164.3, U165.15
MOSI55: TP278.P$1, U167.3, U168.15
MOSI56: TP283.P$1, U170.3, U171.15
MOSI57: TP288.P$1, U173.3, U174.15
MOSI58: TP293.P$1, U176.3, U177.15
MOSI59: TP298.P$1, U179.3, U180.15
unnamed: Q1.1, U1.8
unnamed: Q1.3, U1.7
unnamed: D1.A, R1.2
unnamed: R1.1, U1.9
unnamed: D2.A, R4.2
unnamed: Q2.1, U6.8
unnamed: D3.A, R6.2
unnamed: Q2.3, U6.7
unnamed: D4.A, R5.2
unnamed: R5.1, U6.9
unnamed: D5.A, R8.2
unnamed: Q3.1, U9.8
unnamed: Q3.3, U9.7
unnamed: D6.A, R9.2
unnamed: R9.1, U9.9
unnamed: D7.A, R11.2
unnamed: Q4.1, U12.8
unnamed: Q4.3, U12.7
unnamed: D8.A, R12.2
unnamed: R12.1, U12.9
unnamed: D9.A, R14.2
unnamed: Q5.1, U15.8
unnamed: Q5.3, U15.7
unnamed: D10.A, R15.2
unnamed: R15.1, U15.9
unnamed: D11.A, R17.2
unnamed: Q6.1, U18.8
unnamed: Q6.3, U18.7
unnamed: D12.A, R18.2
unnamed: R18.1, U18.9
unnamed: D13.A, R20.2
unnamed: Q7.1, U21.8
unnamed: Q7.3, U21.7
unnamed: D14.A, R21.2
unnamed: R21.1, U21.9
unnamed: D15.A, R23.2
unnamed: Q8.1, U24.8
unnamed: Q8.3, U24.7
unnamed: D16.A, R24.2
unnamed: R24.1, U24.9
unnamed: D17.A, R26.2
unnamed: Q9.1, U27.8
unnamed: Q9.3, U27.7
unnamed: D18.A, R27.2
unnamed: R27.1, U27.9
unnamed: D19.A, R29.2
unnamed: Q10.1, U30.8
unnamed: Q10.3, U30.7
unnamed: D20.A, R30.2
unnamed: R30.1, U30.9
unnamed: D21.A, R32.2
unnamed: Q11.1, U33.8
unnamed: Q11.3, U33.7
unnamed: D22.A, R33.2
unnamed: R33.1, U33.9
unnamed: D23.A, R35.2
unnamed: Q12.1, U36.8
unnamed: Q12.3, U36.7
unnamed: D24.A, R36.2
unnamed: R36.1, U36.9
unnamed: D25.A, R38.2
unnamed: Q13.1, U39.8
unnamed: Q13.3, U39.7
unnamed: D26.A, R39.2
unnamed: R39.1, U39.9
unnamed: D27.A, R41.2
unnamed: Q14.1, U42.8
unnamed: Q14.3, U42.7
unnamed: D28.A, R42.2
unnamed: R42.1, U42.9
unnamed: D29.A, R44.2
unnamed: Q15.1, U45.8
unnamed: Q15.3, U45.7
unnamed: D30.A, R45.2
unnamed: R45.1, U45.9
unnamed: D31.A, R47.2
unnamed: Q16.1, U48.8
unnamed: Q16.3, U48.7
unnamed: D32.A, R48.2
unnamed: R48.1, U48.9
unnamed: D33.A, R50.2
unnamed: Q17.1, U51.8
unnamed: Q17.3, U51.7
unnamed: D34.A, R51.2
unnamed: R51.1, U51.9
unnamed: D35.A, R53.2
unnamed: Q18.1, U54.8
unnamed: Q18.3, U54.7
unnamed: D36.A, R54.2
unnamed: R54.1, U54.9
unnamed: D37.A, R56.2
unnamed: Q19.1, U57.8
unnamed: Q19.3, U57.7
unnamed: D38.A, R57.2
unnamed: R57.1, U57.9
unnamed: D39.A, R59.2
unnamed: Q20.1, U60.8
unnamed: Q20.3, U60.7
unnamed: D40.A, R60.2
unnamed: R60.1, U60.9
unnamed: D41.A, R62.2
unnamed: Q21.1, U63.8
unnamed: Q21.3, U63.7
unnamed: D42.A, R63.2
unnamed: R63.1, U63.9
unnamed: D43.A, R65.2
unnamed: Q22.1, U66.8
unnamed: Q22.3, U66.7
unnamed: D44.A, R66.2
unnamed: R66.1, U66.9
unnamed: D45.A, R68.2
unnamed: Q23.1, U69.8
unnamed: Q23.3, U69.7
unnamed: D46.A, R69.2
unnamed: R69.1, U69.9
unnamed: D47.A, R71.2
unnamed: Q24.1, U72.8
unnamed: Q24.3, U72.7
unnamed: D48.A, R72.2
unnamed: R72.1, U72.9
unnamed: D49.A, R74.2
unnamed: Q25.1, U75.8
unnamed: Q25.3, U75.7
unnamed: D50.A, R75.2
unnamed: R75.1, U75.9
unnamed: D51.A, R77.2
unnamed: Q26.1, U78.8
unnamed: Q26.3, U78.7
unnamed: D52.A, R78.2
unnamed: R78.1, U78.9
unnamed: D53.A, R80.2
unnamed: Q27.1, U81.8
unnamed: Q27.3, U81.7
unnamed: D54.A, R81.2
unnamed: R81.1, U81.9
unnamed: D55.A, R83.2
unnamed: Q28.1, U84.8
unnamed: Q28.3, U84.7
unnamed: D56.A, R84.2
unnamed: R84.1, U84.9
unnamed: D57.A, R86.2
unnamed: Q29.1, U87.8
unnamed: Q29.3, U87.7
unnamed: D58.A, R87.2
unnamed: R87.1, U87.9
unnamed: D59.A, R89.2
unnamed: Q30.1, U90.8
unnamed: Q30.3, U90.7
unnamed: D60.A, R90.2
unnamed: R90.1, U90.9
unnamed: D61.A, R92.2
unnamed: Q31.1, U93.8
unnamed: Q31.3, U93.7
unnamed: D62.A, R93.2
unnamed: R93.1, U93.9
unnamed: D63.A, R95.2
unnamed: Q32.1, U96.8
unnamed: Q32.3, U96.7
unnamed: D64.A, R96.2
unnamed: R96.1, U96.9
unnamed: D65.A, R98.2
unnamed: Q33.1, U99.8
unnamed: Q33.3, U99.7
unnamed: D66.A, R99.2
unnamed: R99.1, U99.9
unnamed: D67.A, R101.2
unnamed: Q34.1, U102.8
unnamed: Q34.3, U102.7
unnamed: D68.A, R102.2
unnamed: R102.1, U102.9
unnamed: D69.A, R104.2
unnamed: Q35.1, U105.8
unnamed: Q35.3, U105.7
unnamed: D70.A, R105.2
unnamed: R105.1, U105.9
unnamed: D71.A, R107.2
unnamed: Q36.1, U108.8
unnamed: Q36.3, U108.7
unnamed: D72.A, R108.2
unnamed: R108.1, U108.9
unnamed: D73.A, R110.2
unnamed: Q37.1, U111.8
unnamed: Q37.3, U111.7
unnamed: D74.A, R111.2
unnamed: R111.1, U111.9
unnamed: D75.A, R113.2
unnamed: Q38.1, U114.8
unnamed: Q38.3, U114.7
unnamed: D76.A, R114.2
unnamed: R114.1, U114.9
unnamed: D77.A, R116.2
unnamed: Q39.1, U117.8
unnamed: Q39.3, U117.7
unnamed: D78.A, R117.2
unnamed: R117.1, U117.9
unnamed: D79.A, R119.2
unnamed: Q40.1, U120.8
unnamed: Q40.3, U120.7
unnamed: D80.A, R120.2
unnamed: R120.1, U120.9
unnamed: D81.A, R122.2
unnamed: Q41.1, U123.8
unnamed: Q41.3, U123.7
unnamed: D82.A, R123.2
unnamed: R123.1, U123.9
unnamed: D83.A, R125.2
unnamed: Q42.1, U126.8
unnamed: Q42.3, U126.7
unnamed: D84.A, R126.2
unnamed: R126.1, U126.9
unnamed: D85.A, R128.2
unnamed: Q43.1, U129.8
unnamed: Q43.3, U129.7
unnamed: D86.A, R129.2
unnamed: R129.1, U129.9
unnamed: D87.A, R131.2
unnamed: Q44.1, U132.8
unnamed: Q44.3, U132.7
unnamed: D88.A, R132.2
unnamed: R132.1, U132.9
unnamed: D89.A, R134.2
unnamed: Q45.1, U135.8
unnamed: Q45.3, U135.7
unnamed: D90.A, R135.2
unnamed: R135.1, U135.9
unnamed: D91.A, R137.2
unnamed: Q46.1, U138.8
unnamed: Q46.3, U138.7
unnamed: D92.A, R138.2
unnamed: R138.1, U138.9
unnamed: D93.A, R140.2
unnamed: Q47.1, U141.8
unnamed: Q47.3, U141.7
unnamed: D94.A, R141.2
unnamed: R141.1, U141.9
unnamed: D95.A, R143.2
unnamed: Q48.1, U144.8
unnamed: Q48.3, U144.7
unnamed: D96.A, R144.2
unnamed: R144.1, U144.9
unnamed: D97.A, R146.2
unnamed: Q49.1, U147.8
unnamed: Q49.3, U147.7
unnamed: D98.A, R147.2
unnamed: R147.1, U147.9
unnamed: D99.A, R149.2
unnamed: Q50.1, U150.8
unnamed: Q50.3, U150.7
unnamed: D100.A, R150.2
unnamed: R150.1, U150.9
unnamed: D101.A, R152.2
unnamed: Q51.1, U153.8
unnamed: Q51.3, U153.7
unnamed: D102.A, R153.2
unnamed: R153.1, U153.9
unnamed: D103.A, R155.2
unnamed: Q52.1, U156.8
unnamed: Q52.3, U156.7
unnamed: D104.A, R156.2
unnamed: R156.1, U156.9
unnamed: D105.A, R158.2
unnamed: Q53.1, U159.8
unnamed: Q53.3, U159.7
unnamed: D106.A, R159.2
unnamed: R159.1, U159.9
unnamed: D107.A, R161.2
unnamed: Q54.1, U162.8
unnamed: Q54.3, U162.7
unnamed: D108.A, R162.2
unnamed: R162.1, U162.9
unnamed: D109.A, R164.2
unnamed: Q55.1, U165.8
unnamed: Q55.3, U165.7
unnamed: D110.A, R165.2
unnamed: R165.1, U165.9
unnamed: D111.A, R167.2
unnamed: Q56.1, U168.8
unnamed: Q56.3, U168.7
unnamed: D112.A, R168.2
unnamed: R168.1, U168.9
unnamed: D113.A, R170.2
unnamed: Q57.1, U171.8
unnamed: Q57.3, U171.7
unnamed: D114.A, R171.2
unnamed: R171.1, U171.9
unnamed: D115.A, R173.2
unnamed: Q58.1, U174.8
unnamed: Q58.3, U174.7
unnamed: D116.A, R174.2
unnamed: R174.1, U174.9
unnamed: D117.A, R176.2
unnamed: Q59.1, U177.8
unnamed: Q59.3, U177.7
unnamed: D118.A, R177.2
unnamed: R177.1, U177.9
unnamed: D119.A, R179.2
unnamed: Q60.1, U180.8
unnamed: Q60.3, U180.7
unnamed: D120.A, R180.2
unnamed: R180.1, U180.9
RAW: JP2.3, U2.1, U2.3
RAW1: JP1.3, U4.1, U4.3
RAW2: JP3.3, U7.1, U7.3
RAW3: JP4.3, U10.1, U10.3
RAW4: JP5.3, U13.1, U13.3
RAW5: JP6.3, U16.1, U16.3
RAW6: JP7.3, U19.1, U19.3
RAW7: JP8.3, U22.1, U22.3
RAW8: JP9.3, U25.1, U25.3
RAW9: JP10.3, U28.1, U28.3
RAW10: JP11.3, U31.1, U31.3
RAW11: JP12.3, U34.1, U34.3
RAW12: JP13.3, U37.1, U37.3
RAW13: JP14.3, U40.1, U40.3
RAW14: JP15.3, U43.1, U43.3
RAW15: JP16.3, U46.1, U46.3
RAW16: JP17.3, U49.1, U49.3
RAW17: JP18.3, U52.1, U52.3
RAW18: JP19.3, U55.1, U55.3
RAW19: JP20.3, U58.1, U58.3
RAW20: JP21.3, U61.1, U61.3
RAW21: JP22.3, U64.1, U64.3
RAW22: JP23.3, U67.1, U67.3
RAW23: JP24.3, U70.1, U70.3
RAW24: JP25.3, U73.1, U73.3
RAW25: JP26.3, U76.1, U76.3
RAW26: JP27.3, U79.1, U79.3
RAW27: JP28.3, U82.1, U82.3
RAW28: JP29.3, U85.1, U85.3
RAW29: JP30.3, U88.1, U88.3
RAW30: JP31.3, U91.1, U91.3
RAW31: JP32.3, U94.1, U94.3
RAW32: JP33.3, U97.1, U97.3
RAW33: JP34.3, U100.1, U100.3
RAW34: JP35.3, U103.1, U103.3
RAW35: JP36.3, U106.1, U106.3
RAW36: JP37.3, U109.1, U109.3
RAW37: JP38.3, U112.1, U112.3
RAW38: JP39.3, U115.1, U115.3
RAW39: JP40.3, U118.1, U118.3
RAW40: JP41.3, U121.1, U121.3
RAW41: JP42.3, U124.1, U124.3
RAW42: JP43.3, U127.1, U127.3
RAW43: JP44.3, U130.1, U130.3
RAW44: JP45.3, U133.1, U133.3
RAW45: JP46.3, U136.1, U136.3
RAW46: JP47.3, U139.1, U139.3
RAW47: JP48.3, U142.1, U142.3
RAW48: JP49.3, U145.1, U145.3
RAW49: JP50.3, U148.1, U148.3
RAW50: JP51.3, U151.1, U151.3
RAW51: JP52.3, U154.1, U154.3
RAW52: JP53.3, U157.1, U157.3
RAW53: JP54.3, U160.1, U160.3
RAW54: JP55.3, U163.1, U163.3
RAW55: JP56.3, U166.1, U166.3
RAW56: JP57.3, U169.1, U169.3
RAW57: JP58.3, U172.1, U172.3
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
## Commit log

2020-05-22 Uploaded previous work
2020-09-02 Successful build 1
2020-09-03 build1 parts list and connections
2020-09-06 Trying Telemetry
2020-09-09 added documentation
2020-09-12 espcopter codes
2020-09-19 started custom FC code for esp32
2020-09-22 orientation 1 done, RTIMULib started
2020-09-26 Successful mesh test, Uno PPM code
2020-09-26 seperated PPM code
2020-09-27 PPM code now on both esp8266 and esp32
2020-10-03 started vrep simulation
2020-10-03 quadcopter python simulation enabled
2020-10-04 demo swarm
2020-10-05 espnow started
2020-10-05 ESPNOW master-32 multislave-8266 bidirectional
2020-10-09 sound localization with IR sync
2020-10-11 dual core test
2020-10-12 transmitter receiver espnow ppm
